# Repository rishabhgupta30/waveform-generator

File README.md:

# waveform-generator
Waveform generator using KiCAD

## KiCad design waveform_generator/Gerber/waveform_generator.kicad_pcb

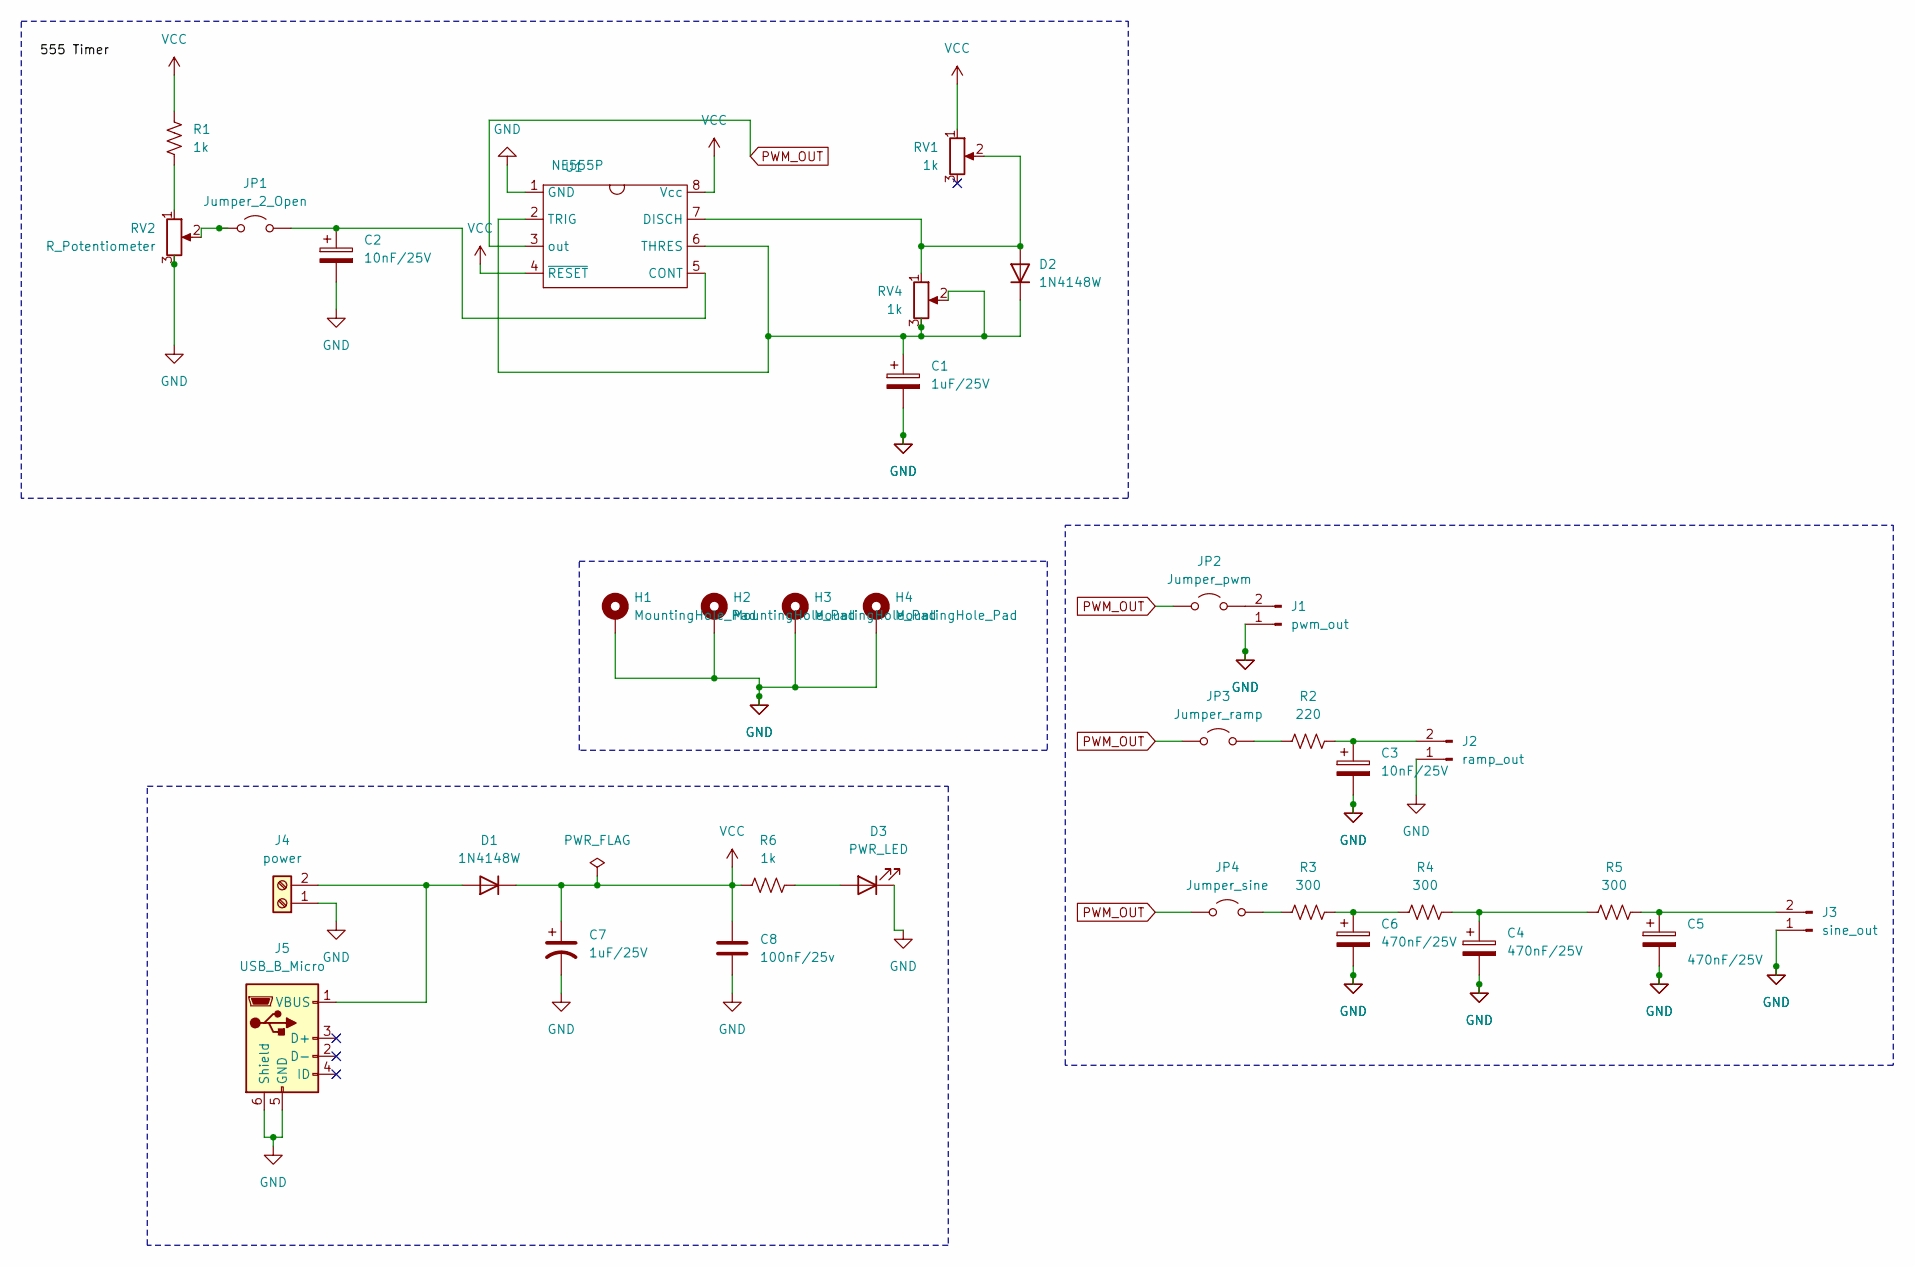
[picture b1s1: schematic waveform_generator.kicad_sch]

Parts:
C1: 1uF/25V; C_0603_1608Metric
C2, C3: 10nF/25V; C_0603_1608Metric
C4, C5, C6: 470nF/25V; C_0603_1608Metric
C7: 1uF/25V; CP_Radial_D5.0mm_P2.50mm
C8: 100nF/25v; D_0603_1608Metric
D1, D2: 1N4148W; D_SOD-123
D3: PWR_LED; LED_0603_1608Metric
H1, H2, H3, H4: MountingHole_Pad; MountingHole_2.2mm_M2_Pad_Via
J1: pwm_out; PinHeader_1x02_P2.54mm_Vertical
J2: ramp_out; PinHeader_1x02_P2.54mm_Vertical
J3: sine_out; PinHeader_1x02_P2.54mm_Vertical
J4: power; TerminalBlock_Phoenix_MKDS-1,5-2-5.08_1x02_P5.08mm_Horizont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
J5: USB_B_Micro; USB_Micro-B_Molex_47346-0001
JP1: Jumper_2_Open; PinHeader_1x02_P2.54mm_Vertical
JP2: Jumper_pwm; PinHeader_1x02_P2.54mm_Vertical
JP3: Jumper_ramp; PinHeader_1x02_P2.54mm_Vertical
JP4: Jumper_sine; PinHeader_1x02_P2.54mm_Vertical
R1, R6: 1k; R_0603_1608Metric
R2: 220; R_0603_1608Metric
R3, R4, R5: 300; R_0603_1608Metric
RV1, RV4: 1k; TRIM_3362P-1-204
RV2: R_Potentiometer; TRIM_3362P-1-204
U1: NE555P; DIP-8_W7.62mm

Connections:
GND: C1.2, C2.2, C3.2, C4.2, C5.2, C6.2, C7.2, C8.2, D3.1 (K), H1.1, H2.1, H3.1, H4.1, J1.1, J2.1, J3.1, J4.1, J5.5 (GND), J5.6 (Shield), RV2.3, U1.1 (GND)
unnamed: C4.1, R4.2, R5.1
unnamed: C6.1, R3.2, R4.1
unnamed: D1.2 (A), J4.2, J5.1 (VBUS)
unnamed: D2.2 (A), RV1.2, RV4.1, U1.7 (DISCH)
unnamed: C1.1, D2.1 (K), RV4.2, RV4.3, U1.2 (TRIG), U1.6 (THRES)
unnamed: D3.2 (A), R6.2
unnamed: J1.2, JP2.2 (B)
unnamed: C3.1, J2.2, R2.2
unnamed: C5.1, J3.2, R5.2
unnamed: JP1.1 (A), RV2.2
unnamed: C2.1, JP1.2 (B), U1.5 (CONT)
unnamed: JP3.2 (B), R2.1
unnamed: JP4.2 (B), R3.1
unnamed: R1.2, RV2.1
PWM_OUT: JP2.1 (A), JP3.1 (A), JP4.1 (A), U1.3 (out)
VCC: C7.1, C8.1, D1.1 (K), R1.1, R6.1, RV1.1, U1.4 (~RESET), U1.8 (Vcc)

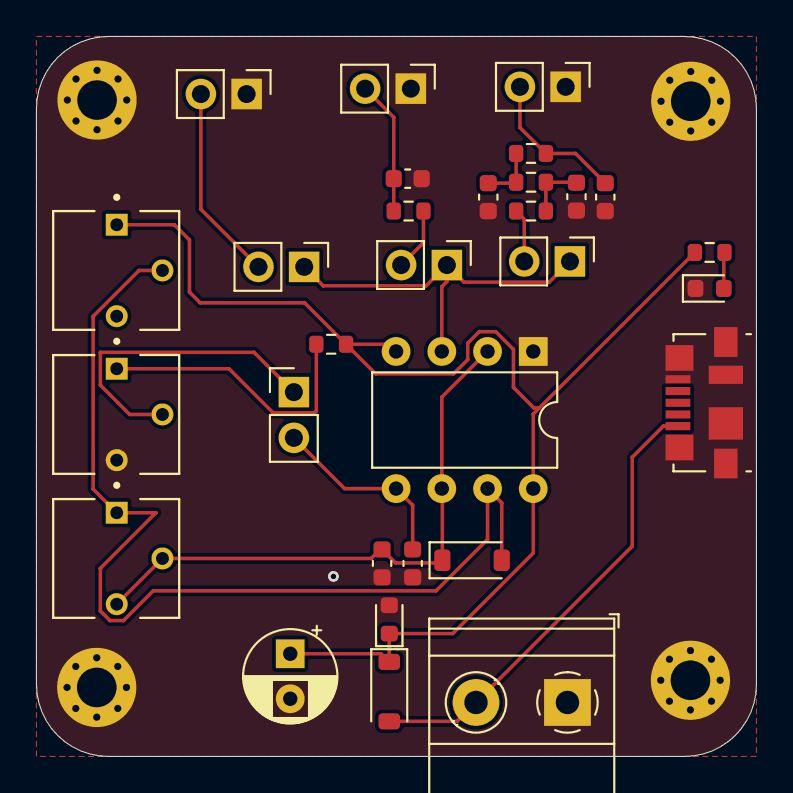
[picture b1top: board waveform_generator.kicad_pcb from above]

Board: 2 copper layers, 40.0 x 40.0 mm, 34 parts (0 on the bottom side), 17 nets.

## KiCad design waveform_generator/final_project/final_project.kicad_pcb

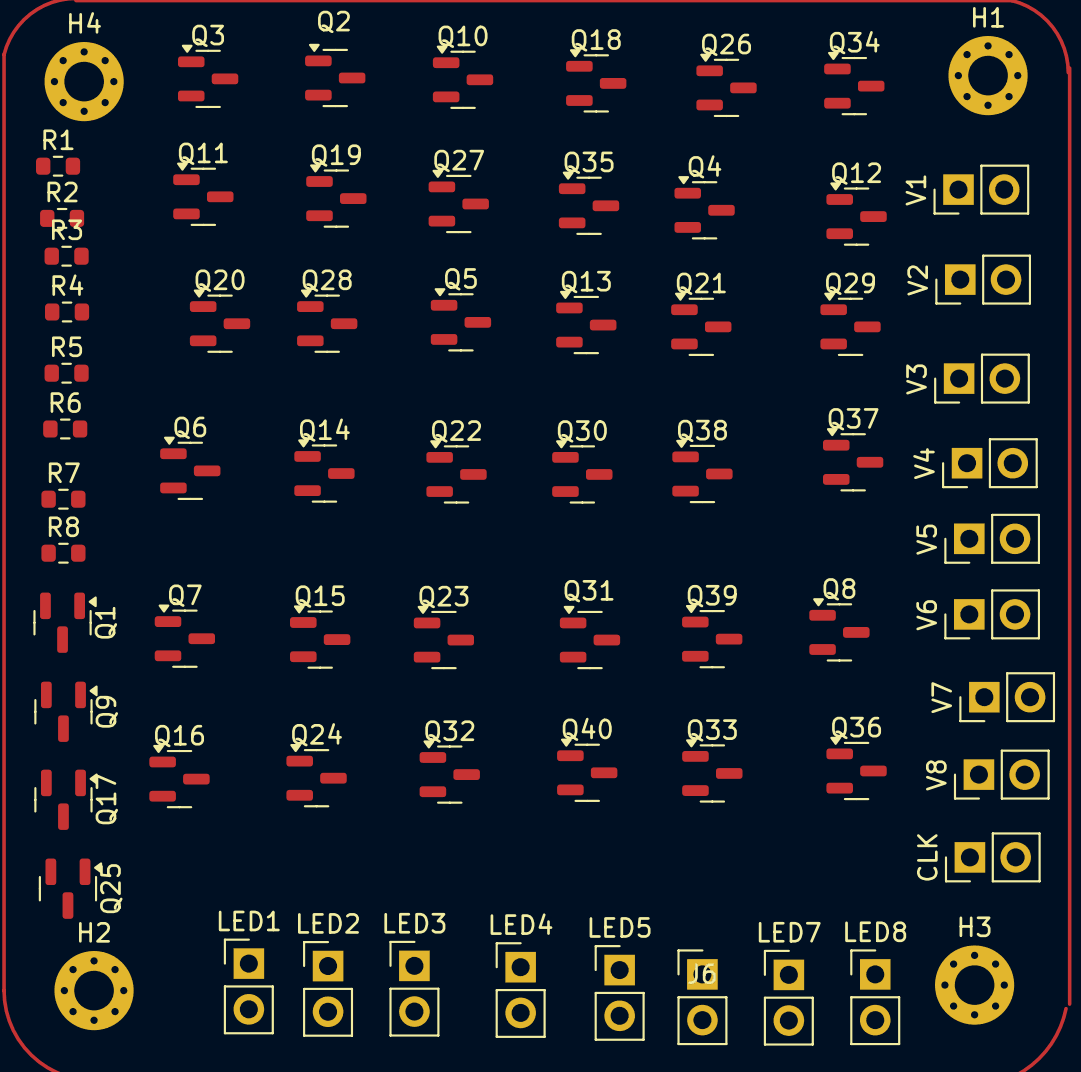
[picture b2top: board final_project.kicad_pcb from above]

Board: 2 copper layers, 69 parts (0 on the bottom side), 43 nets, no tracks yet.

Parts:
CLK: Clk; PinHeader_1x02_P2.54mm_Vertical
H1, H2, H3, H4: MountingHole_Pad; MountingHole_2.2mm_M2_Pad_Via
J6: LED6; PinHeader_1x02_P2.54mm_Vertical
LED1: LED1; PinHeader_1x02_P2.54mm_Vertical
LED2: LED2; PinHeader_1x02_P2.54mm_Vertical
LED3: LED3; PinHeader_1x02_P2.54mm_Vertical
LED4: LED4; PinHeader_1x02_P2.54mm_Vertical
LED5: LED5; PinHeader_1x02_P2.54mm_Vertical
LED7: LED7; PinHeader_1x02_P2.54mm_Vertical
LED8: LED8; PinHeader_1x02_P2.54mm_Vertical
Q1, Q2, Q4, Q6, Q11, Q14, Q16, Q19, Q21, Q24, Q26, Q29, Q31, Q34, Q36, Q39: PMOS; SOT-23
Q3, Q5, Q7, Q8, Q9, Q10, Q12, Q13, Q15, Q17, Q18, Q20, Q22, Q23, Q25, Q27, Q28, Q30, Q32, Q33, Q35, Q37, Q38, Q40: NMOS; SOT-23
R1, R2, R3, R4, R5, R6, R7, R8: R; R_0603_1608Metric
V1: V1; PinHeader_1x02_P2.54mm_Vertical
V2: V3; PinHeader_1x02_P2.54mm_Vertical
V3, V4: V4; PinHeader_1x02_P2.54mm_Vertical
V5: V5; PinHeader_1x02_P2.54mm_Vertical
V6: V6; PinHeader_1x02_P2.54mm_Vertical
V7: V8; PinHeader_1x02_P2.54mm_Vertical
V8: V9; PinHeader_1x02_P2.54mm_Vertical

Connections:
GND: CLK.1, H1.1, H2.1, H3.1, H4.1, J6.1, LED1.1, LED2.1, LED3.1, LED4.1, LED5.1, LED7.1, LED8.1, Q5.3 (S), Q8.3 (S), Q9.3 (S), Q10.3 (S), Q13.3 (S), Q15.3 (S), Q18.3 (S), Q20.3 (S), Q23.3 (S), Q25.3 (S), Q28.3 (S), Q30.3 (S), Q33.3 (S), Q35.3 (S), Q38.3 (S), Q40.3 (S), V1.1, V2.1, V3.1, V4.1, V5.1, V6.1, V7.1, V8.1
unnamed: LED1.2, R1.2
unnamed: LED2.2, R2.2
unnamed: LED3.2, R3.2
unnamed: LED4.2, R6.2
unnamed: LED5.2, R4.2
unnamed: J6.2, R8.2
unnamed: LED7.2, R5.2
unnamed: LED8.2, R7.2
unnamed: CLK.2, Q3.2 (G), Q7.2 (G), Q12.2 (G), Q17.2 (G), Q22.2 (G), Q27.2 (G), Q32.2 (G), Q37.2 (G)
unnamed: Q1.2 (G), Q8.2 (G), V1.2
unnamed: Q2.2 (G), Q5.2 (G), V6.2
unnamed: Q11.2 (G), Q13.2 (G), V2.2
unnamed: Q16.2 (G), Q18.2 (G), V4.2
unnamed: Q21.2 (G), Q23.2 (G), V3.2
unnamed: Q26.2 (G), Q28.2 (G), V7.2
unnamed: Q31.2 (G), Q33.2 (G), V5.2
unnamed: Q36.2 (G), Q38.2 (G), V8.2
unnamed: Q1.1 (D), Q4.2 (G), Q7.1 (D)
unnamed: Q2.1 (D), Q3.1 (D), Q6.2 (G)
unnamed: Q3.3 (S), Q5.1 (D), Q9.2 (G)
unnamed: Q6.1 (D), Q9.1 (D), R2.1
unnamed: Q4.1 (D), Q10.1 (D), R1.1
unnamed: Q7.3 (S), Q8.1 (D), Q10.2 (G)
unnamed: Q11.1 (D), Q12.1 (D), Q14.2 (G)
unnamed: Q12.3 (S), Q13.1 (D), Q15.2 (G)
unnamed: Q14.1 (D), Q15.1 (D), R3.1
unnamed: Q16.1 (D), Q17.1 (D), Q19.2 (G)
unnamed: Q17.3 (S), Q18.1 (D), Q20.2 (G)
unnamed: Q19.1 (D), Q20.1 (D), R6.1
unnamed: Q21.1 (D), Q22.1 (D), Q24.2 (G)
unnamed: Q22.3 (S), Q23.1 (D), Q25.2 (G)
unnamed: Q24.1 (D), Q25.1 (D), R4.1
unnamed: Q26.1 (D), Q27.1 (D), Q29.2 (G)
unnamed: Q27.3 (S), Q28.1 (D), Q30.2 (G)
unnamed: Q29.1 (D), Q30.1 (D), R8.1
unnamed: Q31.1 (D), Q32.1 (D), Q34.2 (G)
unnamed: Q32.3 (S), Q33.1 (D), Q35.2 (G)
unnamed: Q34.1 (D), Q35.1 (D), R5.1
unnamed: Q36.1 (D), Q37.1 (D), Q39.2 (G)
unnamed: Q37.3 (S), Q38.1 (D), Q40.2 (G)
unnamed: Q39.1 (D), Q40.1 (D), R7.1
VDD: Q1.3 (S), Q2.3 (S), Q4.3 (S), Q6.3 (S), Q11.3 (S), Q14.3 (S), Q16.3 (S), Q19.3 (S), Q21.3 (S), Q24.3 (S), Q26.3 (S), Q29.3 (S), Q31.3 (S), Q34.3 (S), Q36.3 (S), Q39.3 (S)
